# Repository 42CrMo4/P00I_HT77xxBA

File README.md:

# HT77xxBA Eval Board

## Goal

The goal of the project will be:
- [ ] **undefined** - not known what the project will bring 
- [x] **learn** - personally learn something new, no usefull outcome expected
- [ ] **prototype** - a working prototype or mvp
- [ ] **80-20-rule** - 80% outcome with 20% effort
- [ ] **Product** - lets see :wink:

## Description. 

| Font                                                                    | Back                                                                      |
|-------------------------------------------------------------------------|---------------------------------------------------------------------------|
|  |  |

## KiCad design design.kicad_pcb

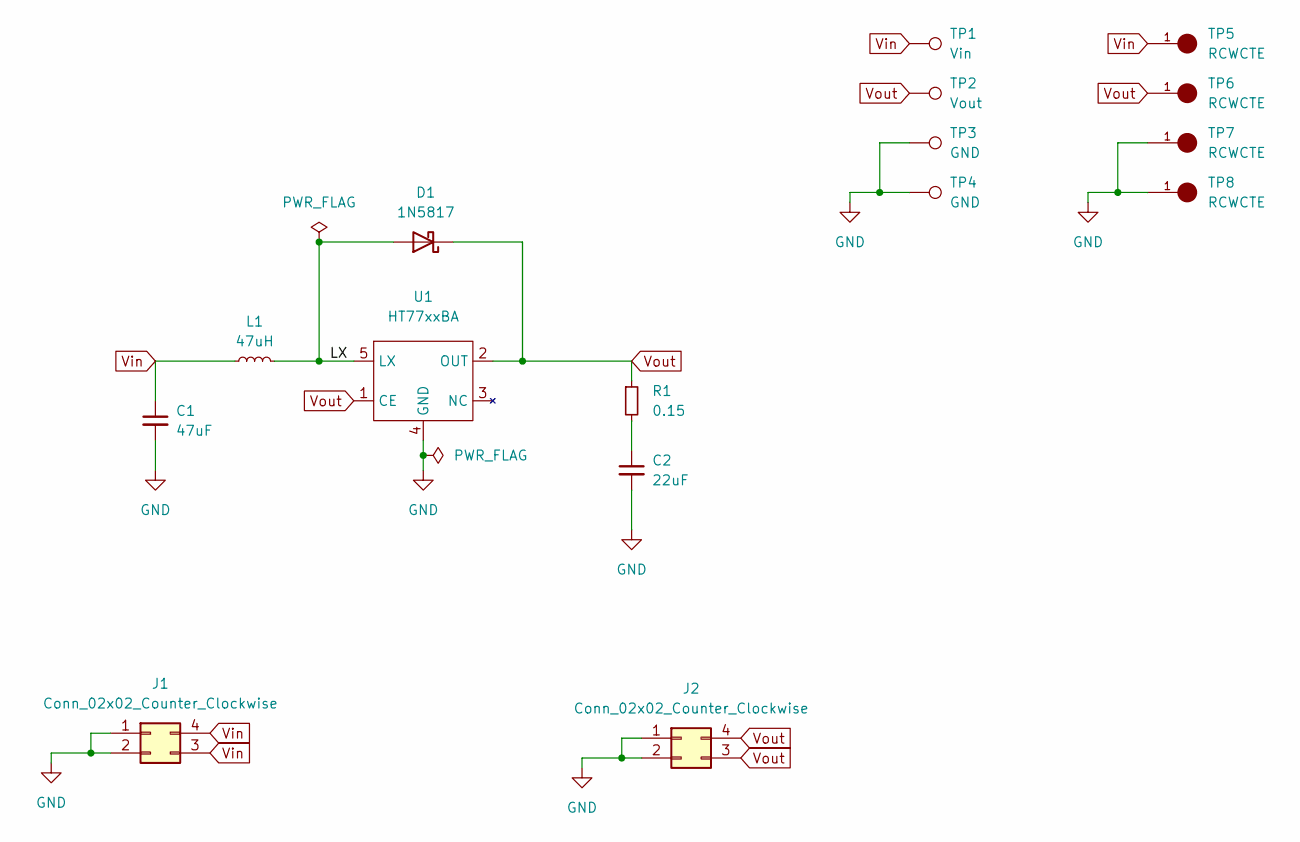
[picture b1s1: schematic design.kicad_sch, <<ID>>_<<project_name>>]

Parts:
C1: 47uF; C_0805_2012Metric
C2: 22uF; C_0805_2012Metric
D1: 1N5817; D_T-1_P10.16mm_Horizontal
J1, J2: Conn_02x02_Counter_Clockwise; PinHeader_2x02_P2.54mm_Vertical
L1: 47uH; L_Vishay_IFSC-1515AH_4x4x1.8mm
R1: 0.15; R_0805_2012Metric
TP1: Vin; TestPoint_Pad_D3.0mm
TP2: Vout; TestPoint_Pad_D3.0mm
TP3, TP4: GND; TestPoint_Pad_D3.0mm
TP5, TP6, TP7, TP8: RCWCTE; RCWCTE_TP420X150; PARTREV 1/06/14
U1: HT77xxBA; SOT-23-5

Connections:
/LX: D1.2 (A), L1.2, U1.5 (LX)
GND: C1.2, C2.2, J1.1, J1.2, J2.1, J2.2, TP3.1, TP4.1, TP7.1, TP8.1, U1.4 (GND)
unnamed: C2.1, R1.2
Vin: C1.1, J1.3, J1.4, L1.1, TP1.1, TP5.1
Vout: D1.1 (K), J2.3, J2.4, R1.1, TP2.1, TP6.1, U1.1 (CE), U1.2 (OUT)

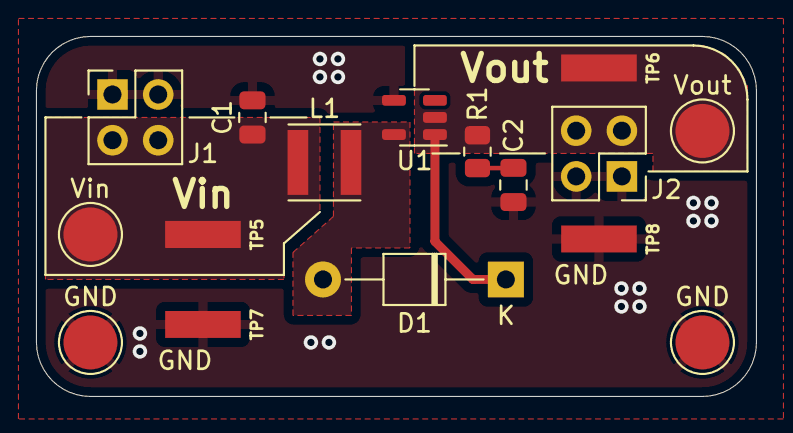
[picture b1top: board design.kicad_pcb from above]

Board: 2 copper layers, 40.0 x 20.0 mm, 16 parts (0 on the bottom side), 5 nets.

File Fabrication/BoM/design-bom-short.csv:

Row,Description,Part,References,Value,Footprint,Quantity Per PCB,Status,Datasheet,PARTREV,SNAPEDA_PN,MANUFACTURER,MAXIMUM_PACKAGE_HEIGHT,STANDARD
1,"Unpolarized capacitor, small symbol",C_Small,C2,22uF,C_0805_2012Metric,1, ,~,,,,,
2,"Unpolarized capacitor, small symbol",C_Small,C1,47uF,C_0805_2012Metric,1, ,~,,,,,
3,Schottky diode,D_Schottky,D1,1N5817,D_T-1_P10.16mm_Horizontal,1, ,~,,,,,
4,"Generic connector, double row, 02x02, counter clockwise pin numbering scheme (similar to DIP package numbering), script generated (kicad-library-utils/schlib/autogen/connector/)",Conn_02x02_Counter_Clockwise,J1 J2,Conn_02x02_Counter_Clockwise,PinHeader_2x02_P2.54mm_Vertical,2, ,~,,,,,
5,"Inductor, small symbol",L_Small,L1,47uH,L_Vishay_IFSC-1515AH_4x4x1.8mm,1, ,~,,,,,
6,"Resistor, small symbol",R_Small,R1,0.15,R_0805_2012Metric,1, ,~,,,,,
7,,HT77xxBA,U1,HT77xxBA,SOT-23-5,1, ,,,,,,

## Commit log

2025-01-26 DEL template Stuff and Add basic infos
2025-01-26 Update Bom and PCB_top
2025-01-26 release notes und checklist
2025-01-26 Archive & Renew release docs
